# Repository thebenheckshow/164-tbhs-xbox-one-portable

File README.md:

# 164-tbhs-xbox-one-portable
Files for creating a portable xbox one

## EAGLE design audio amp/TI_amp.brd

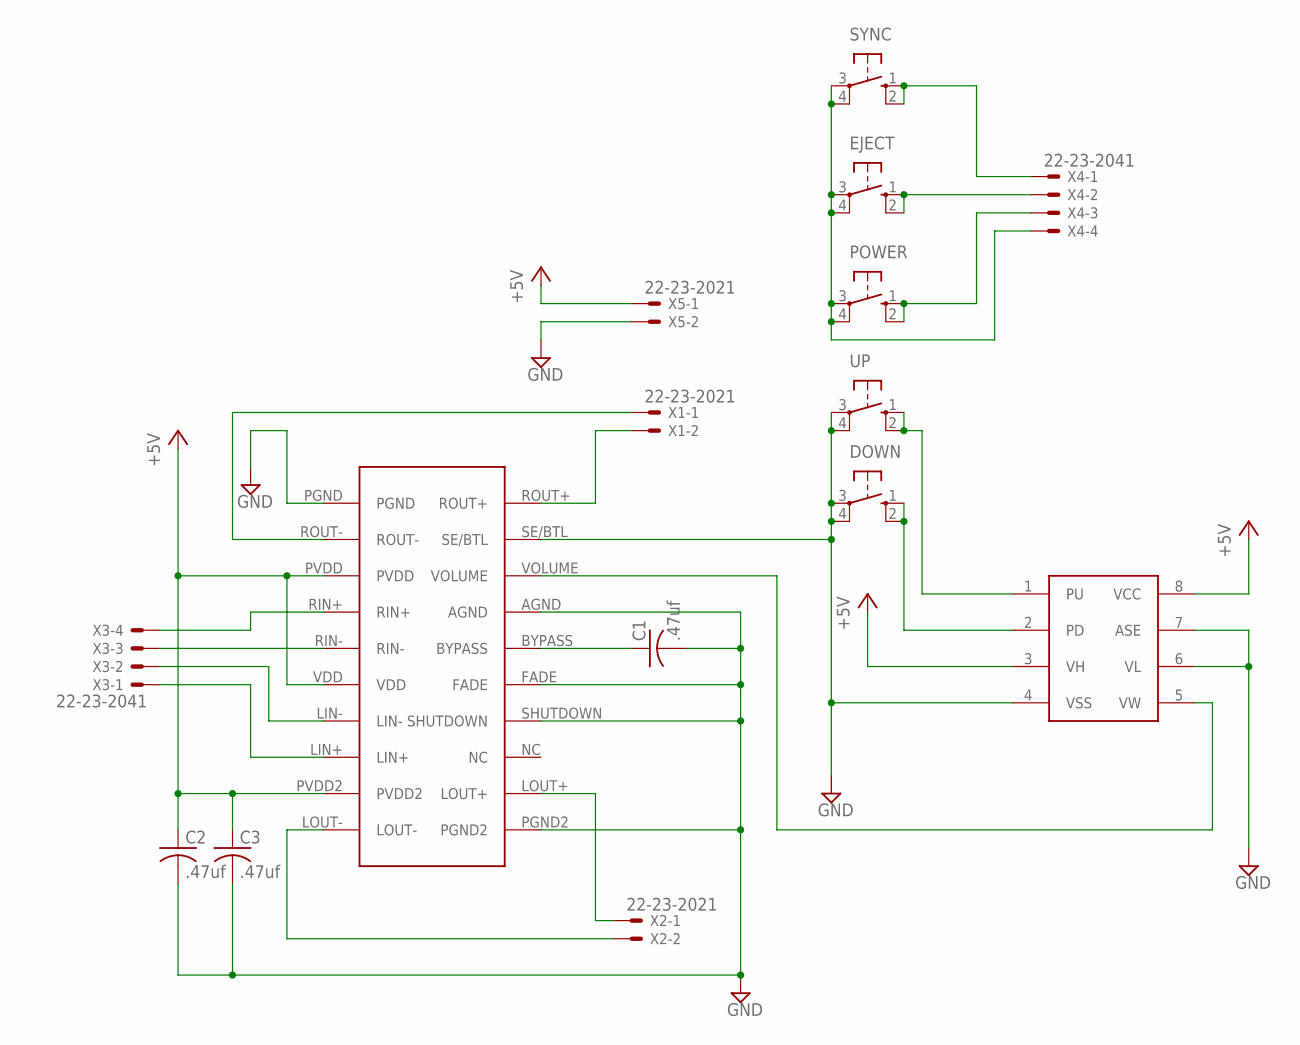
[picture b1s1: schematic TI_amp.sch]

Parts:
C1, C2, C3: .47uf; C1206
DOWN: 10-XX; B3F-10XX
EJECT: 10-XX; B3F-10XX
POWER: 10-XX; B3F-10XX
SYNC: 10-XX; B3F-10XX
U$1: TPA6021A4; DIP-20
U$2: X9511; SOIC-8
UP: 10-XX; B3F-10XX
X1, X2, X5: 22-23-2021
X3, X4: 22-23-2041

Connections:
+5V: C2.1, C3.1, U$1.PVDD, U$1.PVDD2, U$1.VDD, U$2.3 (VH), U$2.8 (VCC), X5.1
GND: C1.2, C2.2, C3.2, DOWN.3, DOWN.4 (P1), U$1.AGND, U$1.FADE, U$1.PGND, U$1.PGND2, U$1.SE/BTL, U$1.SHUTDOWN, U$2.4 (VSS), U$2.6 (VL), U$2.7 (ASE), UP.3, UP.4 (P1), X5.2
unnamed: DOWN.1 (S), DOWN.2 (S1), U$2.2 (PD)
unnamed: U$2.1 (PU), UP.1 (S), UP.2 (S1)
unnamed: U$1.VOLUME, U$2.5 (VW)
unnamed: EJECT.3, EJECT.4 (P1), POWER.3, POWER.4 (P1), SYNC.3, SYNC.4 (P1), X4.4
unnamed: POWER.1 (S), POWER.2 (S1), X4.3
unnamed: C1.1, U$1.BYPASS
unnamed: EJECT.1 (S), EJECT.2 (S1), X4.2
unnamed: U$1.ROUT+, X1.2
unnamed: U$1.ROUT-, X1.1
unnamed: U$1.LOUT+, X2.1
unnamed: U$1.LOUT-, X2.2
unnamed: SYNC.1 (S), SYNC.2 (S1), X4.1
unnamed: U$1.RIN+, X3.4
unnamed: U$1.RIN-, X3.3
unnamed: U$1.LIN-, X3.2
unnamed: U$1.LIN+, X3.1

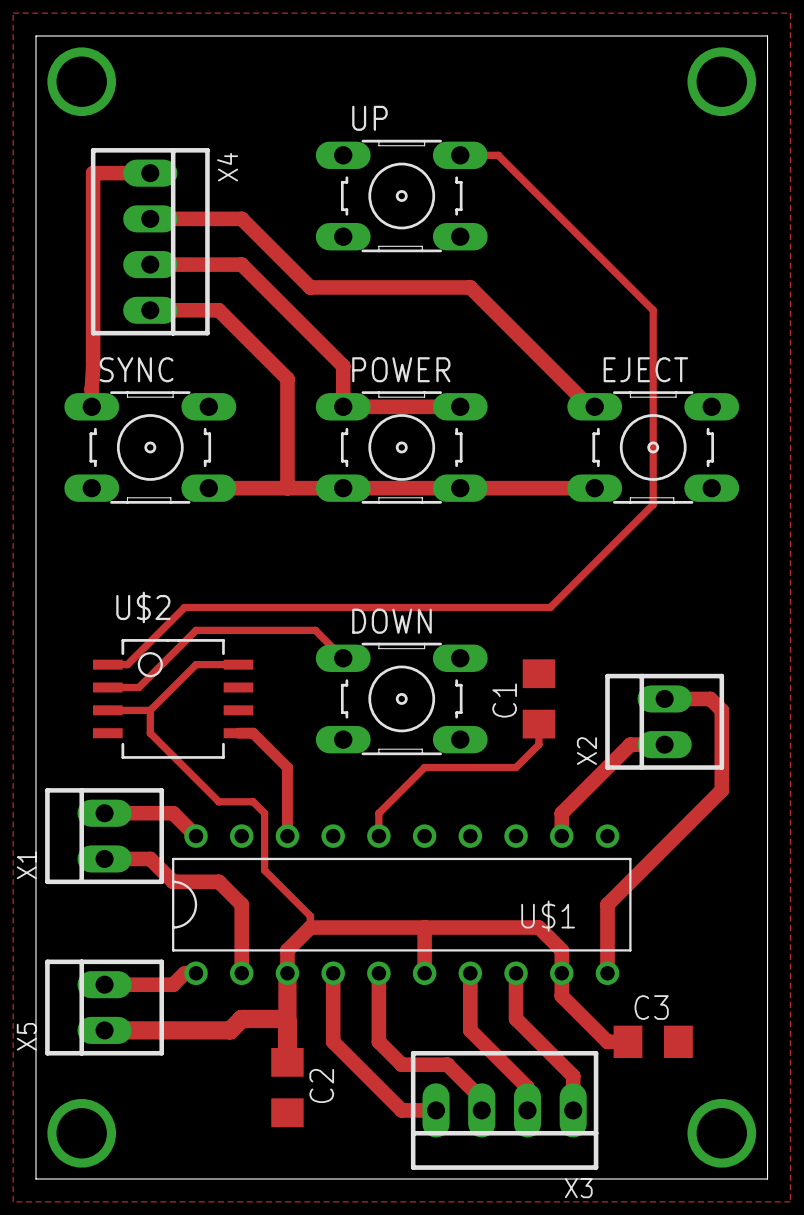
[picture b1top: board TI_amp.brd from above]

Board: 2 copper layers, 40.6 x 63.5 mm, 15 parts (0 on the bottom side), 18 nets.

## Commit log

2015-08-13 Initial test.
